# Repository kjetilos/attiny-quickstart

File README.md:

# attiny-quickstart
eagle schematic and board layout for an attiny2313 quickstart pcb

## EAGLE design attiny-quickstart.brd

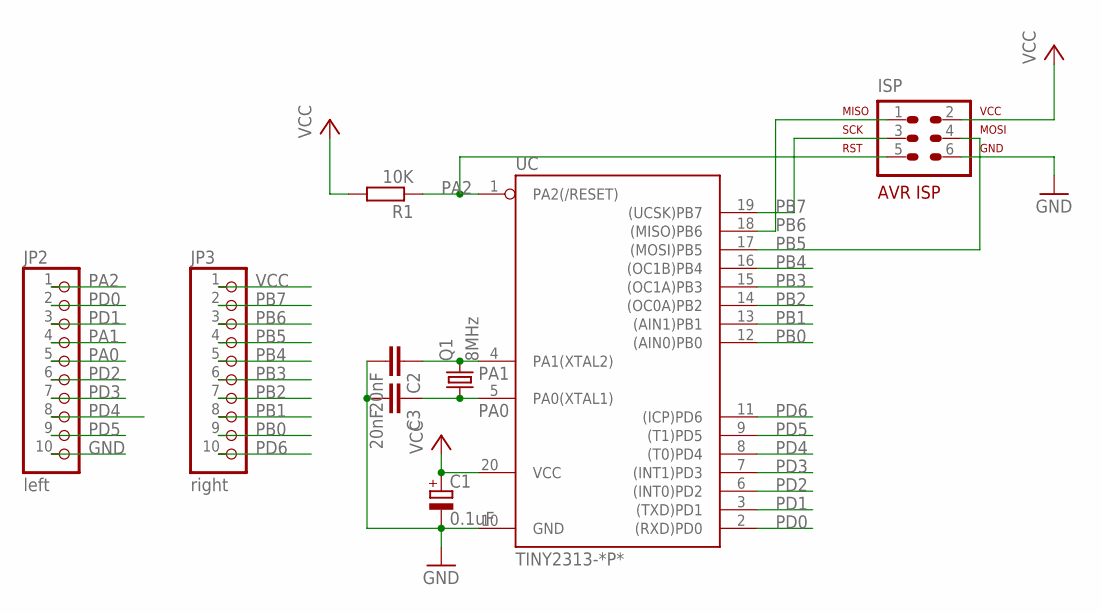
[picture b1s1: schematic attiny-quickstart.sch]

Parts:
C1: 0.1uF; E2,5-6E
C2, C3: 20nF; C025-024X044
ISP: AVR-ISP-6VERT; AVR-ISP-6
JP2: left; 1X10
JP3: right; 1X10
Q1: 8MHz; HC49/S
R1: 10K; 0204/5
UC: TINY2313-*P*; DIL20

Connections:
GND: C1.-, C2.2, C3.2, ISP.6, JP2.10, UC.10 (GND)
PA0: C3.1, JP2.5, Q1.1, UC.5 (PA0(XTAL1))
PA1: C2.1, JP2.4, Q1.2, UC.4 (PA1(XTAL2))
PA2: ISP.5, JP2.1, R1.1, UC.1 (PA2(/RESET))
PB0: JP3.9, UC.12 ((AIN0)PB0)
PB1: JP3.8, UC.13 ((AIN1)PB1)
PB2: JP3.7, UC.14 ((OC0A)PB2)
PB3: JP3.6, UC.15 ((OC1A)PB3)
PB4: JP3.5, UC.16 ((OC1B)PB4)
PB5: ISP.4, JP3.4, UC.17 ((MOSI)PB5)
PB6: ISP.1, JP3.3, UC.18 ((MISO)PB6)
PB7: ISP.3, JP3.2, UC.19 ((UCSK)PB7)
PD0: JP2.2, UC.2 ((RXD)PD0)
PD1: JP2.3, UC.3 ((TXD)PD1)
PD2: JP2.6, UC.6 ((INT0)PD2)
PD3: JP2.7, UC.7 ((INT1)PD3)
PD4: JP2.8, UC.8 ((T0)PD4)
PD5: JP2.9, UC.9 ((T1)PD5)
PD6: JP3.10, UC.11 ((ICP)PD6)
VCC: C1.+, ISP.2, JP3.1, R1.2, UC.20 (VCC)

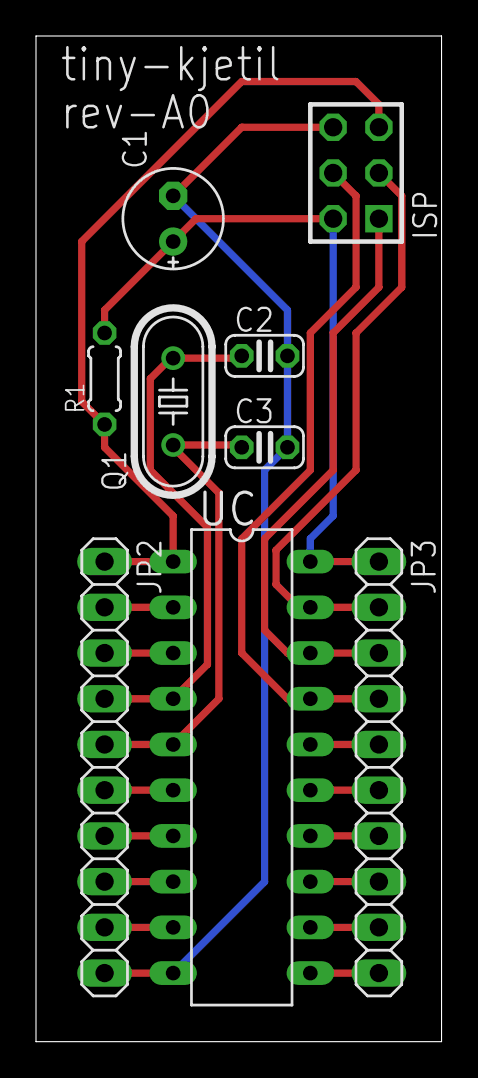
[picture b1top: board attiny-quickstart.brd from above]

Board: 2 copper layers, 22.5 x 55.9 mm, 9 parts (0 on the bottom side), 20 nets.

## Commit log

2015-08-04 Adding the schematic and board
